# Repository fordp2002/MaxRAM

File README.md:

# MaxRAM
Open Hardware BBC RAM/ROM Board

My current thoughts are a board that covers the BBCs 4 sideways ROM sockets and has the following features:
1 4 MBit (512KB) 32 Pin DIP Flash Chip (Socketed) [Microchip Technology SST39SF040-70-4C-PHE]
1 4 Mbit (512KB) SRAM Chip [Alliance Memory, Inc. AS6C4008-55PCN]
1 PLD to handle the logic [ATF1502ASL-25JU44-ND]
1 Simple diode battery backup circuit and battery connector or maybe an IC [DS1210S+TRL-ND] for Battery Backup.

Slot 15 will contain the ROM Manager.
8 Slots will be Write Protected RAM.
8 Slots will be Read Write RAM.
16 pages of Flash will be selected at power on with the ability to switch to 16 pages of RAM after boot.

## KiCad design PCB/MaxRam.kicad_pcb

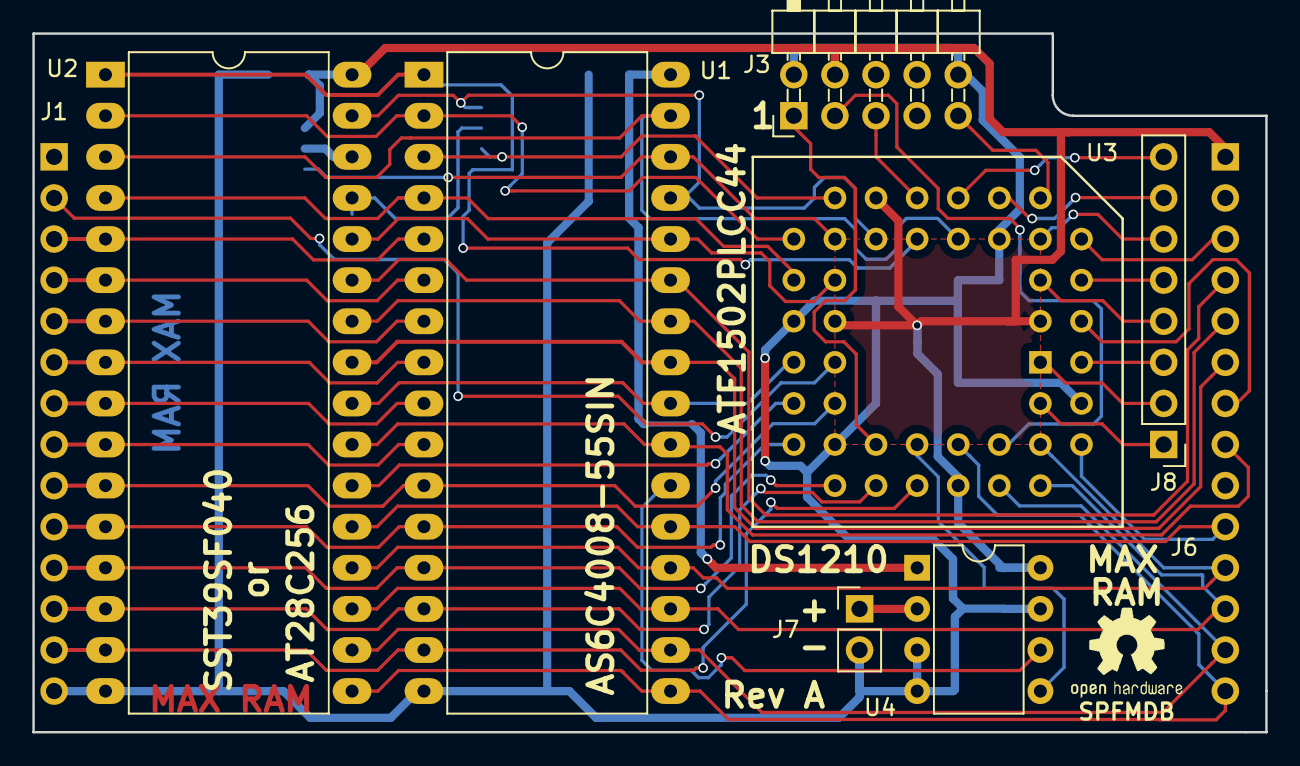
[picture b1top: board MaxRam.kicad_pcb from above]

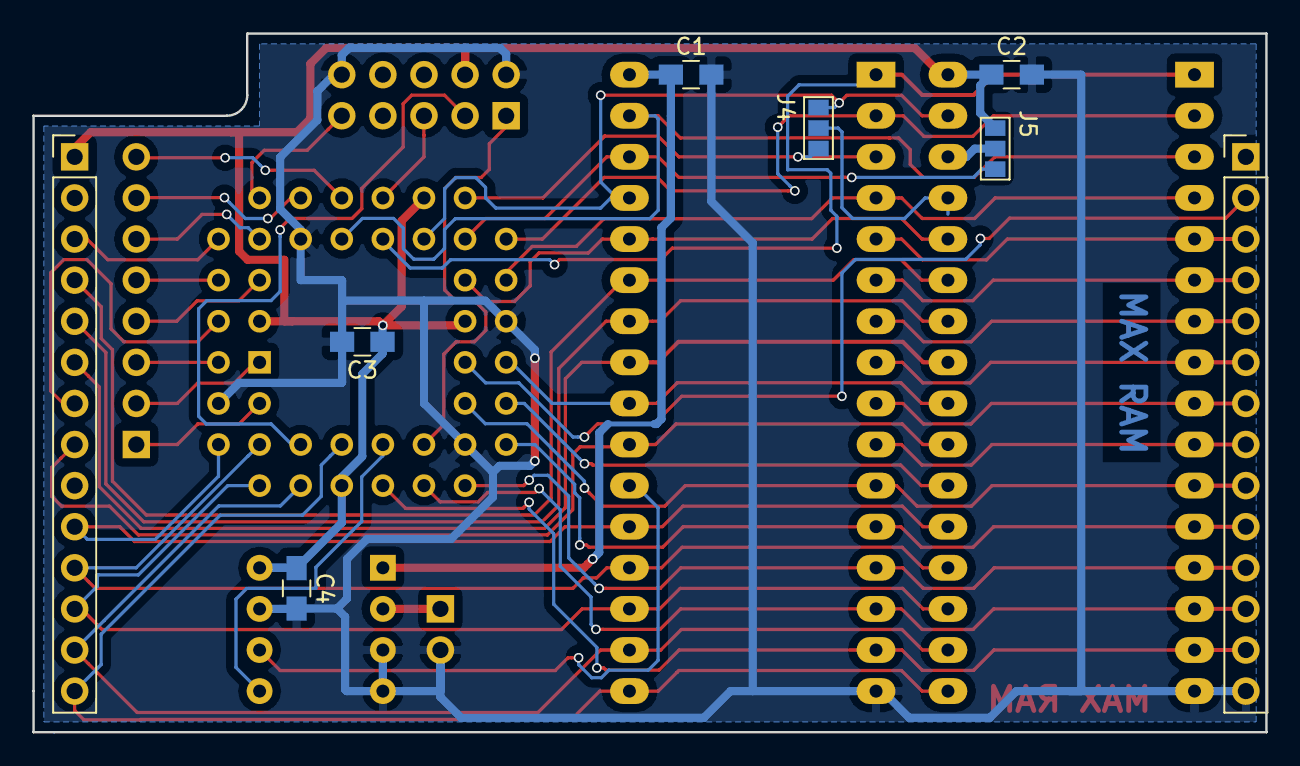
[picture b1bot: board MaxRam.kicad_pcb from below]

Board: 2 copper layers, 76.2 x 43.2 mm, 15 parts (8 on the bottom side), 53 nets.

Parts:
C1, C2, C3, C4: C; C_0805_HandSoldering
J1, J6: CONN_01X14; Pin_Header_Straight_1x14_Pitch2.54mm
J3: CONN_02X05; Pin_Header_Angled_2x05_Pitch2.54mm
J4, J5: GS3
J7: CONN_01X02; Pin_Header_Straight_1x02_Pitch2.54mm
J8: CONN_01X08; Pin_Header_Straight_1x08_Pitch2.54mm
U1: AS6C4008-55SIN; DIP-32_W15.24mm_LongPads
U2: SST39SF040; DIP-32_W15.24mm_LongPads
U3: ATF1502PLCC44; PLCC44
U4: DS1210; DIP-8_W7.62mm

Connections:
+5V: C2.1, C3.1, C4.1, J3.4, J5.1, J6.1, U2.32, U3.3, U3.15, U3.23, U3.35, U4.8
/A0: J1.10, U1.12, U2.12, U3.28
/A1: J1.9, U1.11, U2.11, U3.27
/A2: J1.8, U1.10, U2.10
/A3: J1.7, U1.9, U2.9
/A4: J1.6, U1.8, U2.8
/A5: J1.5, U1.7, U2.7
/A6: J1.4, U1.6, U2.6
/A7: J1.3, U1.5, U2.5
/A8: J6.4, U1.27, U2.27
/A9: J6.5, U1.26, U2.26
/A10: J6.8, U1.23, U2.23
/A11: J6.6, U1.25, U2.25
/A12: J1.2, U3.25
/A13: J6.3, U3.6
/BAT: J7.1, U4.2
/CLK: J8.1, U3.43
/CS_in: J8.8, U3.11
/CsIn: J8.2, U3.1
/D0: J1.11, U1.13, U2.13, U3.29
/D1: J1.12, U1.14, U2.14, U3.31
/D2: J1.13, U1.15, U2.15, U3.33
/D3: J6.14, U1.17, U2.17, U3.36
/D4: J6.13, U1.18, U2.18, U3.37
/D5: J6.12, U1.19, U2.19, U3.39
/D6: J6.11, U1.20, U2.20, U3.41
/D7: J6.10, U1.21, U2.21, U3.40
/FLASH_nCE: U2.22, U3.26
/OE_IN: J6.7, U3.2
/PIN29: J4.2, U2.29
/PIN30: J5.2, U2.30
/RAM_nCE: U1.22, U4.6
/Romsel: J8.3, U3.44
/S12: U1.4, U2.4, U3.20
/S13: U1.28, U2.28, U3.21
/S14: J4.3, U1.3, U3.17
/S15: U1.31, U2.3, U3.12
/S16: U1.2, U2.2, U3.18
/S17: J5.3, U1.30, U3.19
/S18: U1.1, U2.1, U3.14
/TCK: J3.1, U3.32
/TDI: J3.9, U3.7
/TDO: J3.3, U3.38
/TMS: J3.5, U3.13
/VBAT: C1.1, U1.32, U4.1
/Z1: J8.4, U3.5
/Z2: J8.5, U3.4
/Z3: J8.6, U3.8
/Z4: J8.7, U3.9
/nOE: U1.24, U2.24, U3.24
/nWE: J4.1, U1.29, U2.31, U3.16
GND: C1.2, C2.2, C3.2, C4.2, J1.14, J3.2, J3.10, J7.2, U1.16, U2.16, U3.10, U3.22, U3.30, U3.42, U4.3, U4.4, U4.7
unnamed: U3.34, U4.5

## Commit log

2017-04-06 Add some content to the ReadMe
2017-04-06 Add datasheet
2017-04-06 Add Data
2017-04-07 Add more reference reading
2017-04-13 More useful reading
2017-04-16 Add more reading and first go at HDL
2017-04-17 Add the BBC Circuit diagram
2017-04-17 Add KiCad Files
2017-04-17 Update PCB Still getting used to KiCad / PCB Design
2017-04-18 Create LICENSE.txt
    Software License
2017-04-19 Assembly code to erase and byte-program SST39SF010A flash
2017-04-19 Add PCB with CPLD at rats nest
2017-04-20 PCB all routed
2017-04-22 PCB now has a ground plane (copper pour)
2017-04-22 Latest PCB including plane and pin swapped CPLD, still messy
2017-04-26 Work in progress, about to fix overlapping parts
2017-04-27 Latest design. PLCC now on it's own, a bit more tweaking yet.
2017-04-28 All fixed up version
2017-04-30 Post up Issue A as sent to OSH Park
2017-04-30 Update HDL to match the latest design. Very basic design at the moment.
2017-05-18 Fix compiler warnings in the pld file
2017-06-07 Latest tweaks
